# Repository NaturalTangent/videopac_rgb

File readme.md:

# Videopac G7000 RGB Video

This is a PCB providing RGB video output for a PAL VideoPac G7000.

Created using kicad 6.0.0

_Note: This is untested - I'm waiting for PCBs to arrive..._

## Schematic

The schematic is copied from https://gamesx.com/wiki/doku.php?id=av:g7000_av

## PCB

The PCB measures 80mm X 40.6mm.

## BOM

[videopac_rgb_bom.csv](videopac_rgb_bom.csv "BOM")

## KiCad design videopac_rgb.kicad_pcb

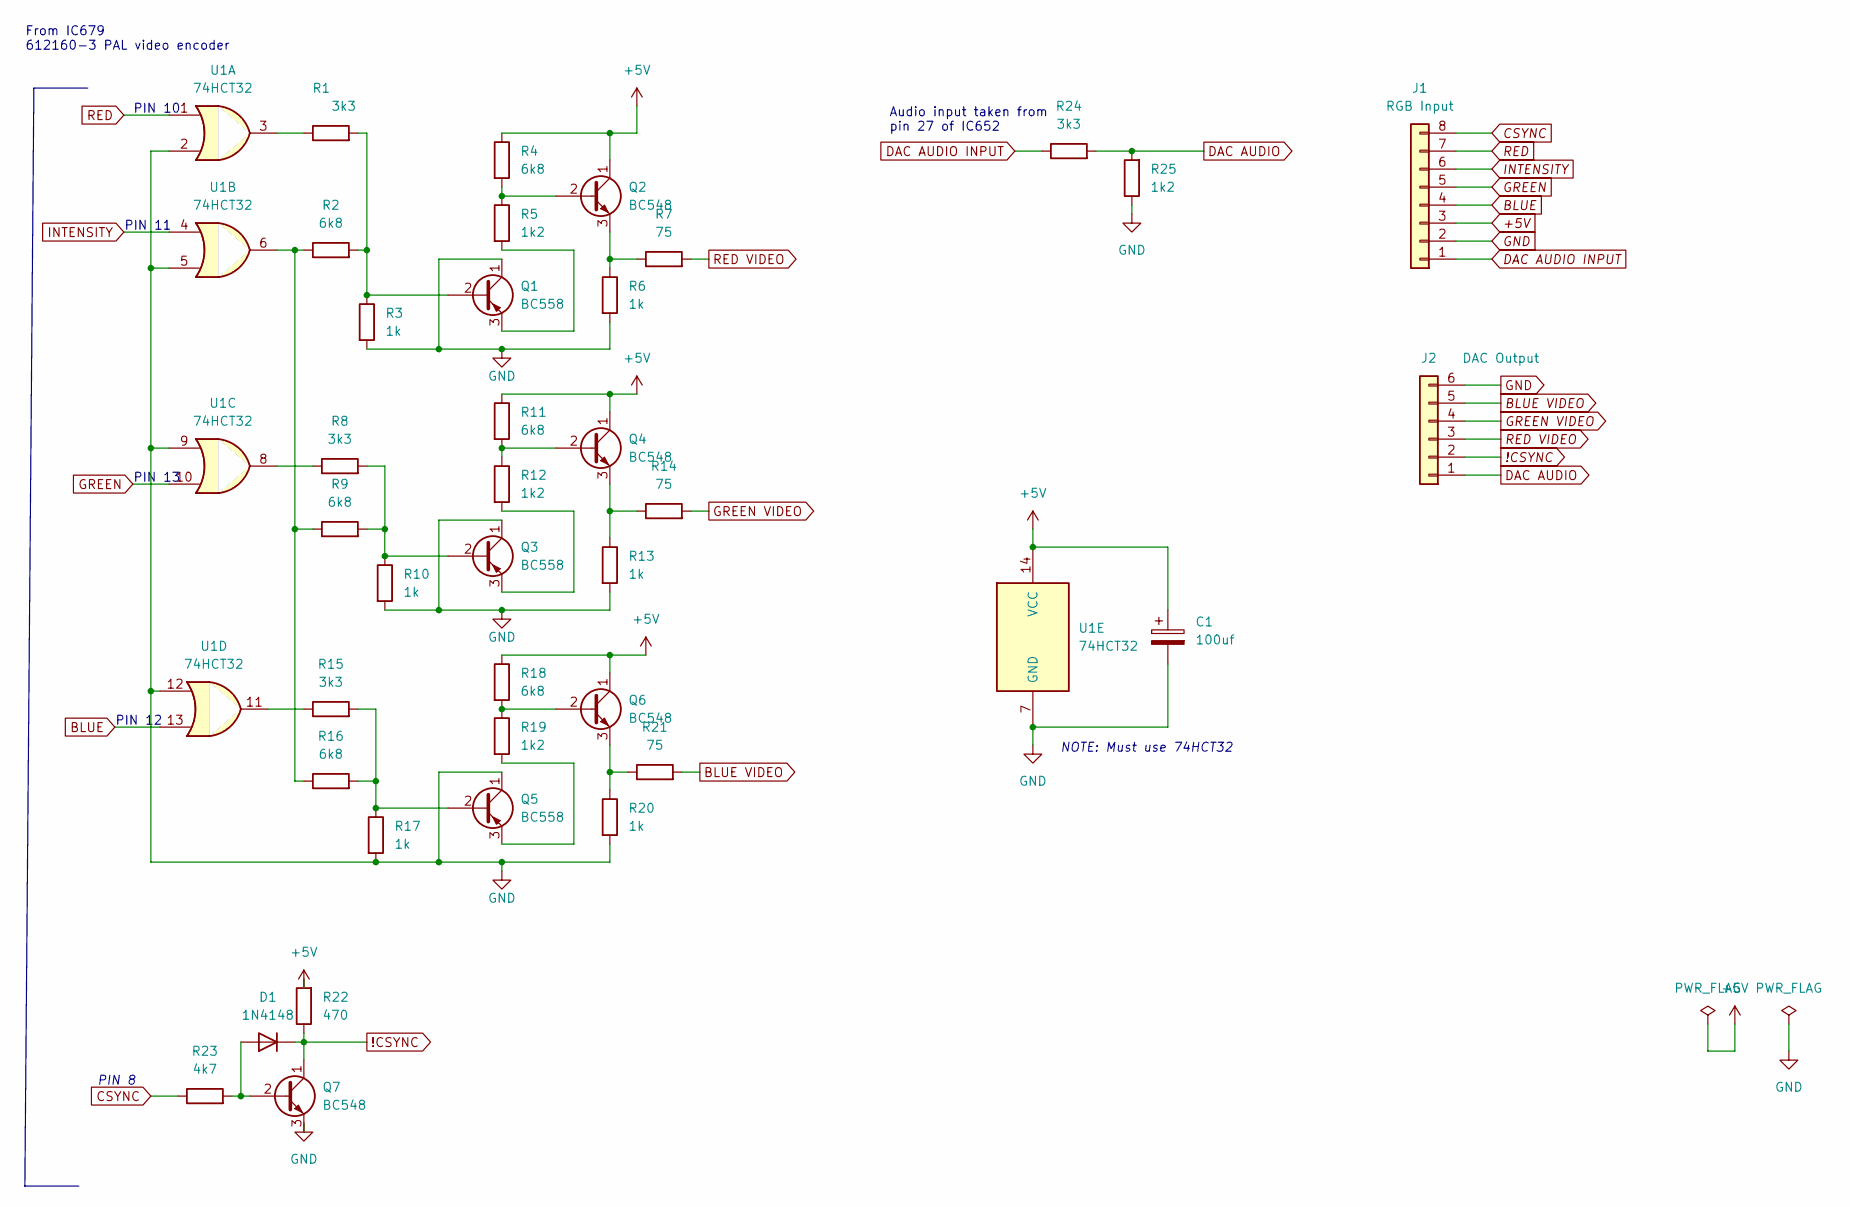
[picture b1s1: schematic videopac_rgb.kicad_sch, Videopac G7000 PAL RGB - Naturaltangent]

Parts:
C1: 100uf; CP_Radial_D5.0mm_P2.00mm
D1: 1N4148; D_DO-35_SOD27_P7.62mm_Horizontal
J1: RGB Input; PinHeader_1x08_P2.54mm_Horizontal
J2: DAC Output; PinHeader_1x06_P2.54mm_Horizontal
Q1, Q3, Q5: BC558; TO-92_Inline
Q2, Q4, Q6, Q7: BC548; TO-92_Inline
R1, R8, R15, R24: 3k3; R_Axial_DIN0207_L6.3mm_D2.5mm_P10.16mm_Horizontal
R2, R4, R9, R11, R16, R18: 6k8; R_Axial_DIN0207_L6.3mm_D2.5mm_P10.16mm_Horizontal
R3, R6, R10, R13, R17, R20: 1k; R_Axial_DIN0207_L6.3mm_D2.5mm_P10.16mm_Horizontal
R5, R12, R19, R25: 1k2; R_Axial_DIN0207_L6.3mm_D2.5mm_P10.16mm_Horizontal
R7, R14, R21: 75; R_Axial_DIN0207_L6.3mm_D2.5mm_P10.16mm_Horizontal
R22: 470; R_Axial_DIN0207_L6.3mm_D2.5mm_P10.16mm_Horizontal
R23: 4k7; R_Axial_DIN0207_L6.3mm_D2.5mm_P10.16mm_Horizontal
U1: 74HCT32; DIP-14_W10.16mm

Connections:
!CSYNC: D1.1 (K), J2.2, Q7.1 (C), R22.1
+5V: C1.1, J1.3, Q2.1 (C), Q4.1 (C), Q6.1 (C), R4.1, R11.1, R18.1, R22.2, U1.14 (VCC)
BLUE: J1.4, U1.13
BLUE VIDEO: J2.5, R21.2
CSYNC: J1.8, R23.1
DAC AUDIO: J2.1, R24.2, R25.2
DAC AUDIO INPUT: J1.1, R24.1
GND: C1.2, J1.2, J2.6, Q1.1 (C), Q3.1 (C), Q5.1 (C), Q7.3 (E), R3.2, R6.2, R10.2, R13.2, R17.2, R20.2, R25.1, U1.2, U1.5, U1.7 (GND), U1.9, U1.12
GREEN: J1.5, U1.10
GREEN VIDEO: J2.4, R14.2
INTENSITY: J1.6, U1.4
unnamed: D1.2 (A), Q7.2 (B), R23.2
unnamed: Q1.2 (B), R1.2, R2.2, R3.1
unnamed: Q1.3 (E), R5.2
unnamed: Q2.2 (B), R4.2, R5.1
unnamed: Q2.3 (E), R6.1, R7.1
unnamed: Q3.2 (B), R10.1
unnamed: Q3.3 (E), R12.2
unnamed: Q4.2 (B), R11.2, R12.1
unnamed: Q4.3 (E), R13.1, R14.1
unnamed: Q5.2 (B), R15.2, R16.2, R17.1
unnamed: Q5.3 (E), R19.2
unnamed: Q6.2 (B), R18.2, R19.1
unnamed: Q6.3 (E), R20.1, R21.1
unnamed: R1.1, U1.3
unnamed: R8.1, U1.8
unnamed: R8.2, R9.2
unnamed: R15.1, U1.11
unnamed: R2.1, R9.1, R16.1, U1.6
RED: J1.7, U1.1
RED VIDEO: J2.3, R7.2

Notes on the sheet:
Audio input taken from pin 27 of IC652
PIN 10
PIN 13
PIN 12
PIN 8
PIN 11
From IC679 612160-3 PAL video encoder
NOTE: Must use 74HCT32

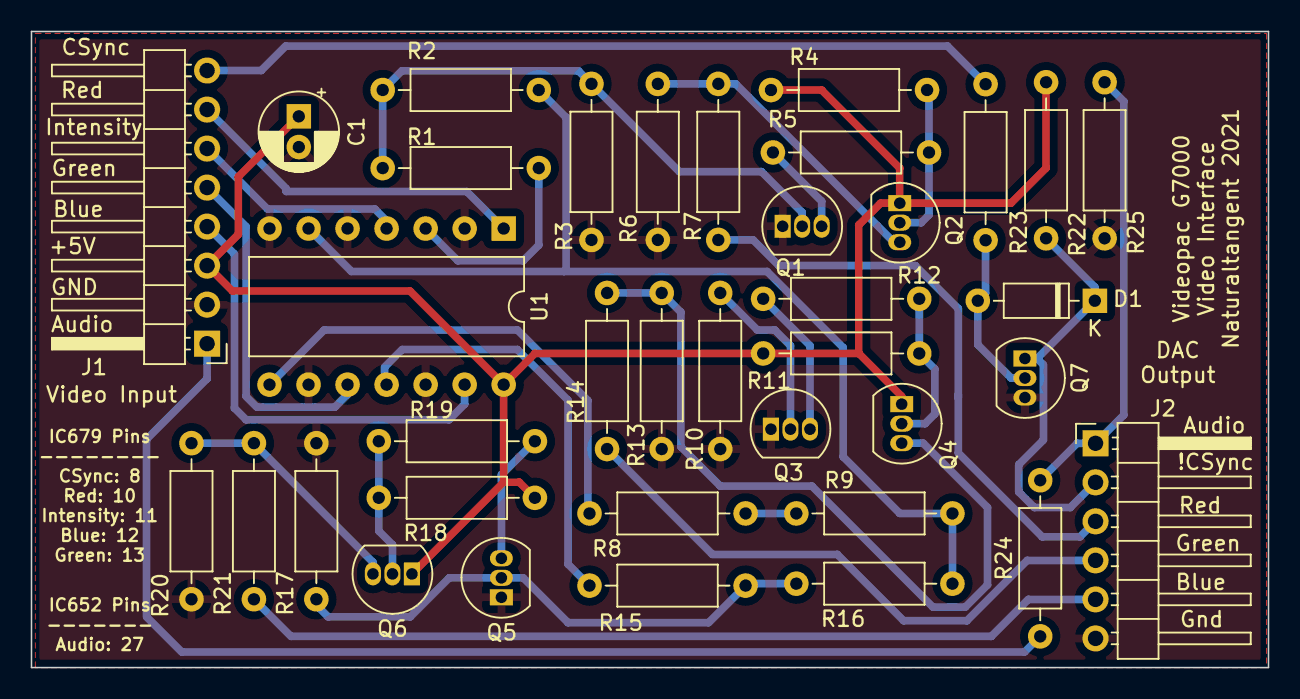
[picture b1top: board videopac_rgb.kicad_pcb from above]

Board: 2 copper layers, 80.5 x 41.4 mm, 37 parts (0 on the bottom side), 31 nets.

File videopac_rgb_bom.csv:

"Id";"Designator";"Package";"Quantity";"Designation";"Supplier and ref";
1;"Q4,Q7,Q6,Q2";"TO-92_Inline";4;"BC548";;;
2;"Q1,Q3,Q5";"TO-92_Inline";3;"BC558";;;
3;"R11,R16,R9,R4,R2,R18";"R_Axial_DIN0207_L6.3mm_D2.5mm_P10.16mm_Horizontal";6;"6k8";;;
4;"R5,R25,R19,R12";"R_Axial_DIN0207_L6.3mm_D2.5mm_P10.16mm_Horizontal";4;"1k2";;;
5;"R10,R17,R20,R6,R13,R3";"R_Axial_DIN0207_L6.3mm_D2.5mm_P10.16mm_Horizontal";6;"1k";;;
6;"R1,R15,R8,R24";"R_Axial_DIN0207_L6.3mm_D2.5mm_P10.16mm_Horizontal";4;"3k3";;;
7;"J1";"PinHeader_1x08_P2.54mm_Horizontal";1;"RGB Input";;;
8;"R23";"R_Axial_DIN0207_L6.3mm_D2.5mm_P10.16mm_Horizontal";1;"4k7";;;
9;"R14,R21,R7";"R_Axial_DIN0207_L6.3mm_D2.5mm_P10.16mm_Horizontal";3;"75";;;
10;"R22";"R_Axial_DIN0207_L6.3mm_D2.5mm_P10.16mm_Horizontal";1;"470";;;
11;"J2";"PinHeader_1x06_P2.54mm_Horizontal";1;"DAC Output";;;
12;"C1";"CP_Radial_D5.0mm_P2.00mm";1;"100uf";;;
13;"U1";"DIP-14_W10.16mm";1;"74HCT32";;;
14;"D1";"D_DO-35_SOD27_P7.62mm_Horizontal";1;"1N4148";;;

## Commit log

2021-12-31 Initial commit of Philips Videopac G7000 RGB video PCB. Untested, waiting for boards to arrive.
2021-12-31 Added bill of materials.
2022-01-14 Add additional ground connection.
